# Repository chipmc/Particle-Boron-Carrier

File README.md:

# Particle-Boron-Carrier-v1.8
This is a carrier board for 3rd Generation Particle Devices (Boron and Argon).  It is intended to support use in outdoor environments and remote locations.  It includes the following capabilities:
* ESD and Short protection (Fuse, TVS and Varistors)
* Support for Solar charging (Large by-pass cap on DC-In and TMP-32 temp sensor to manage safe charging)
* Programmable Watchdog timer (AB1805)
* Real Time Clock with backup to the main LiPO battery (AB1805)
* On/Off switch using a high-side P-MOSFETS
* User Button for custom usage
* Connectors for IO including compatibility with Spankfun Qwiic and Adafruit Stemma (JST ST/SR)
* Footprint for a LoRA Radio module

Key Pin definitions for the FeatherWing Pins
 * Left Side (16 pins)
 Left Side (16 pins)
 * !RESET -
 * 3.3V -
 * !MODE -
 * GND -
 * D19 - A0 -               
 * D18 - A1 -               
 * D17 - A2 -               
 * D16 - A3 -
 * D15 - A4 -               Internal (TMP32) Temp Sensor
 * D14 - A5 / SPI SS -      RFM9x
 * D13 - SCK - SPI Clock -  
 * D12 - MO - SPI MOSI -    RFM9x
 * D11 - MI - SPI MISO -    RFM9x
 * D10 - UART RX -
 * D9 - UART TX -

 Right Size (12 pins)
 * Li+
 * ENABLE
 * VUSB -
 * D8 -                     Wake Connected to Watchdog Timer
 * D7 -                     Blue Led
 * D6 -                     
 * D5 -                     
 * D4 -                     User Switch
 * D3 -
 * D2 -                     RFM9x
 * D1 - SCL - I2C Clock -   FRAM / RTC and I2C Bus
 * D0 - SDA - I2C Data -    FRAM / RTX and I2C Bus

To see minimal code that will exercise the carrier board see this repository:
https://github.com/chipmc/CarrierTest3rdGen

 This board was developed in partnership with the Particle community See this thread for details on this board's development:
 https://community.particle.io/t/boron-xenon-argon-carrier-for-outdoor-applications/48750/213

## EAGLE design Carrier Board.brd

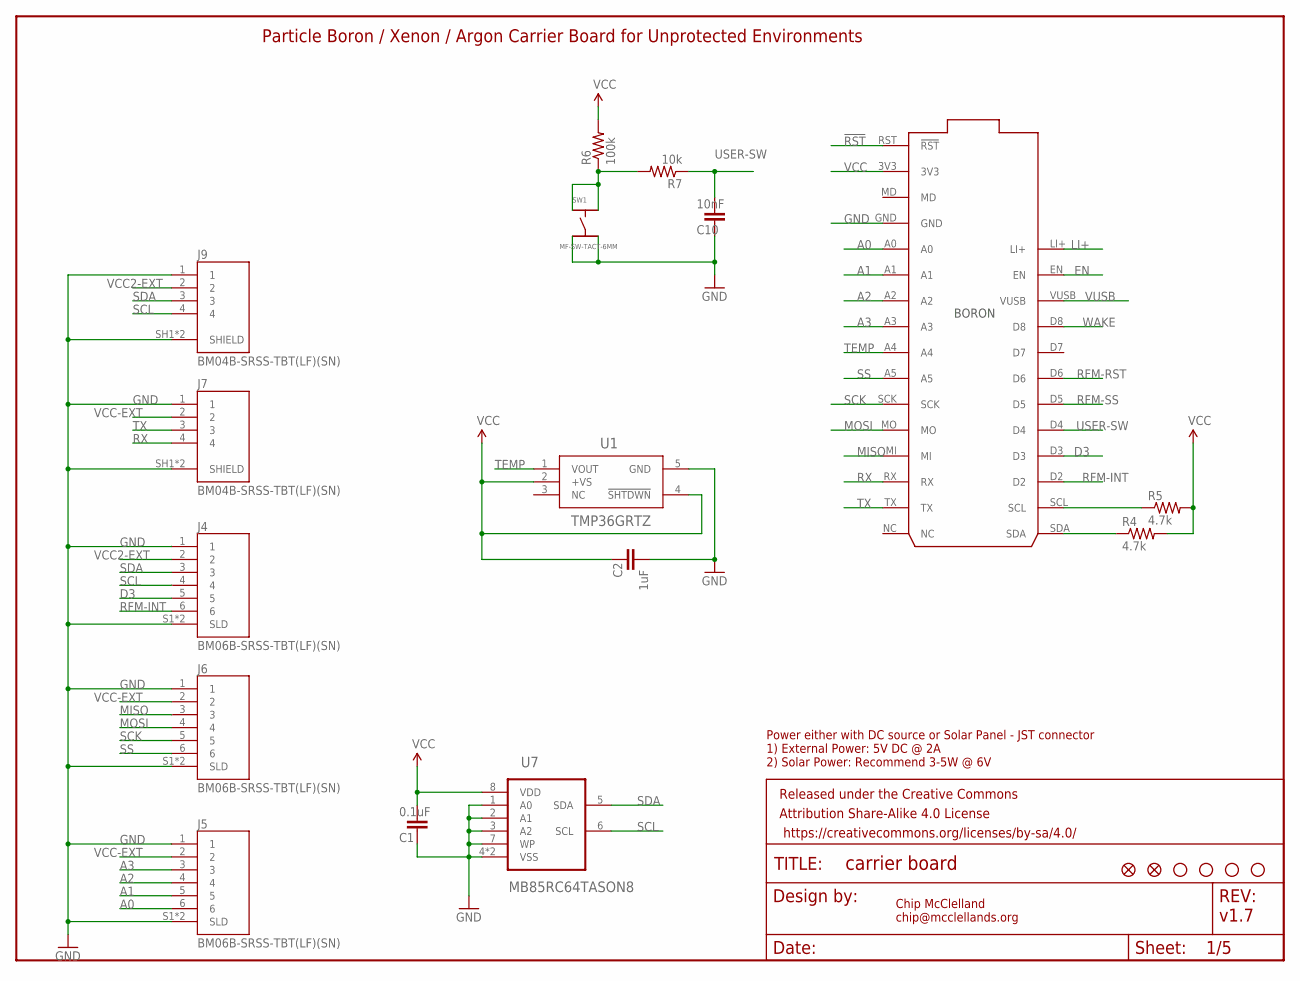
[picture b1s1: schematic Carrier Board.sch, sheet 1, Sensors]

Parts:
C1: 0.1uF; 0805@1; MPN MF-CAP-0805-0.1uF
C2: 1uF; 0805@1; MPN MF-CAP-0805-1uF
C10: 10nF; 0805@1; MPN 08051C103K4T2A
FD1, FD2: FIDUCIALUFIDUCIAL; FIDUCIAL-MICRO
FRAME1: FRAME-LETTER; CREATIVE_COMMONS
J4, J5, J6: BM06B-SRSS-TBT(LF)(SN); JST_BM06B-SRSS-TB(LF)(SN)
J7, J9: BM04B-SRSS-TBT(LF)(SN); CONN_BM04B-SRSS-TBT(LF)(SN)
JP3, JP4, JP5, JP6: STAND-OFF
P1: Particle Boron / Xenon / Argon; PARTICLE-DEVICES_BORON
R4, R5: 4.7k; 0805; MPN MF-RES-0805-4.7K
R6: 100k; 0805; MPN MF-RES-0805-100K
R7: 10k; 0805; MPN MF-RES-0805-10K
SW1: MF-SW-TACT-6MM; TACT6MM
U1: TMP36GRTZ; RJ_5_ADI; MANUFACTURER_PART_NUMBER TMP36GRTZ-REEL7
U7: MB85RC64TASON8; SON50P200X300X75-9N

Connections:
!RST: P1.RST (!RST); also elsewhere on the board
A0: J5.6, P1.A0
A1: J5.5, P1.A1
A2: J5.4, P1.A2
A3: J5.3, P1.A3
D3: J4.5, P1.D3; also elsewhere on the board
EN: P1.EN; also elsewhere on the board
GND: C1.2, C2.2, C10.2, J4.1, J4.S1 (SLD), J4.S2 (SLD), J5.1, J5.S1 (SLD), J5.S2 (SLD), J6.1, J6.S1 (SLD), J6.S2 (SLD), J7.1, J7.SH1 (SHIELD), J7.SH2 (SHIELD), J9.1, J9.SH1 (SHIELD), J9.SH2 (SHIELD), P1.GND, SW1.P$3, SW1.P$4, U1.5 (GND), U7.1 (A0), U7.2 (A1), U7.3 (A2), U7.4 (VSS), U7.7 (WP), U7.9 (VSS); also elsewhere on the board
LI+: P1.LI+; also elsewhere on the board
MISO: J6.3, P1.MI; also elsewhere on the board
MOSI: J6.4, P1.MO; also elsewhere on the board
unnamed: R6.1, R7.2, SW1.P$1, SW1.P$2
RFM-INT: J4.6, P1.D2; also elsewhere on the board
RFM-RST: P1.D6; also elsewhere on the board
RFM-SS: P1.D5; also elsewhere on the board
RX: J7.4, P1.RX
SCK: J6.5, P1.SCK; also elsewhere on the board
SCL: J4.4, J9.4, P1.SCL, R5.1, U7.6 (SCL); also elsewhere on the board
SDA: J4.3, J9.3, P1.SDA, R4.1, U7.5 (SDA); also elsewhere on the board
SS: J6.6, P1.A5
TEMP: P1.A4, U1.1 (VOUT)
TX: J7.3, P1.TX
USER-SW: C10.1, P1.D4, R7.1
VCC: C1.1, C2.1, P1.3V3, R4.2, R5.2, R6.2, U1.2 (+VS), U1.4 (!SHTDWN), U7.8 (VDD); also elsewhere on the board
VCC2-EXT: J4.2, J9.2; also elsewhere on the board
VCC-EXT: J5.2, J6.2, J7.2; also elsewhere on the board
VUSB: P1.VUSB; also elsewhere on the board
WAKE: P1.D8; also elsewhere on the board

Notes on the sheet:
Chip McClelland chip@mcclellands.org
v1.7
Power either with DC source or Solar Panel - JST connector 1) External Power: 5V DC @ 2A 2) Solar Power: Recommend 3-5W @ 6V
Particle Boron / Xenon / Argon Carrier Board for Unprotected Environments

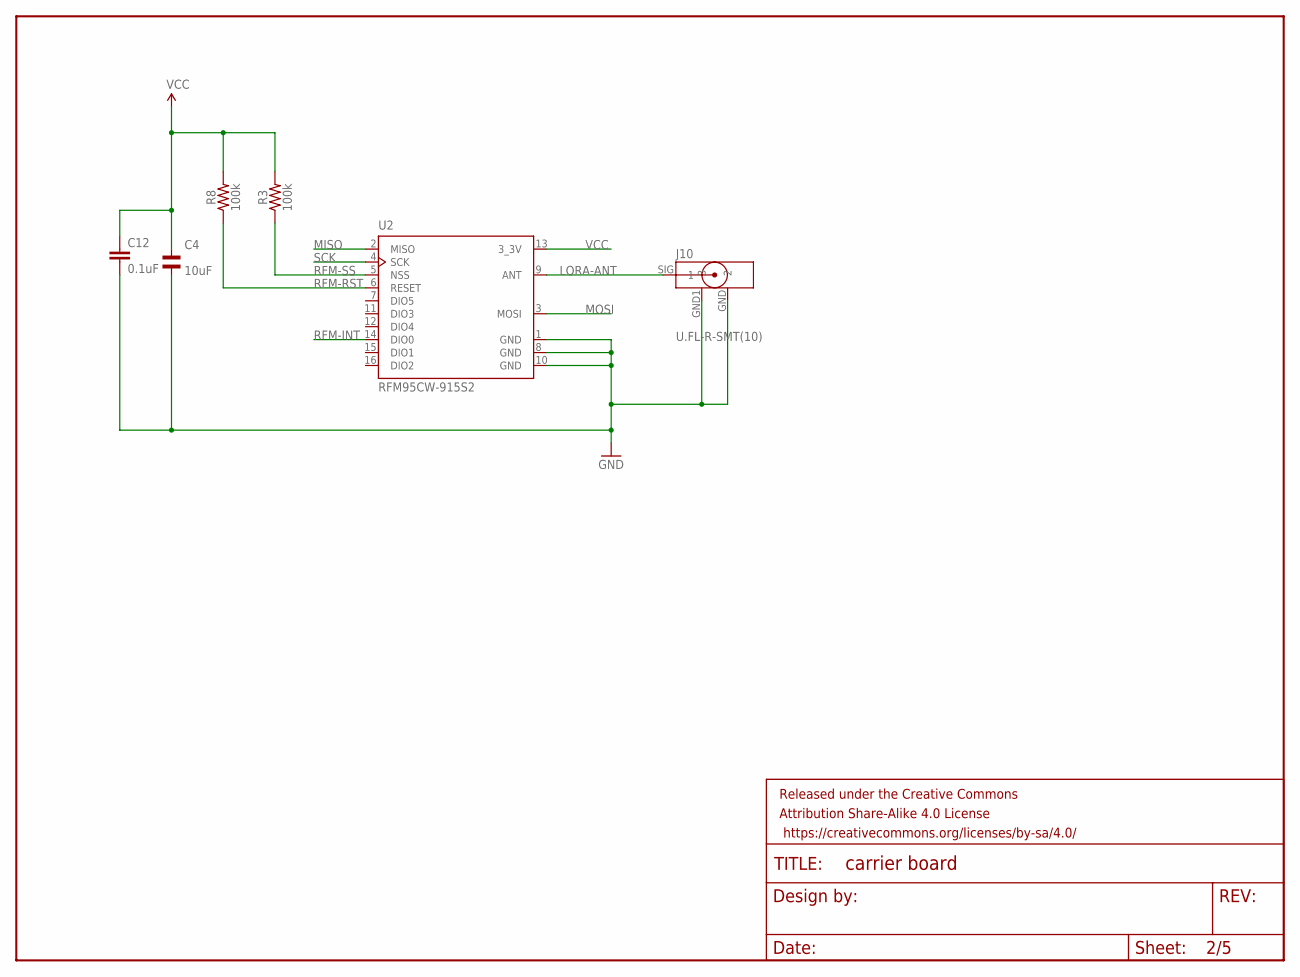
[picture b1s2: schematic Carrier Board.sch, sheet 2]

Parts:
C4: 10uF; C1206
C12: 0.1uF; 0805@1
FRAME4: FRAME-LETTERNO_PACKAGE; DUMMY
J10: U.FL-R-SMT(10)
R3, R8: 100k; 0805
U2: RFM95CW-915S2; XCVR_RFM95W-868S2

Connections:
GND: C4.P$2, C12.2, J10.GND (2), J10.GND1 (3), U2.1 (GND), U2.8 (GND), U2.10 (GND); also elsewhere on the board
LORA-ANT: J10.SIG (1), U2.9 (ANT)
MISO: U2.2 (MISO); also elsewhere on the board
MOSI: U2.3 (MOSI); also elsewhere on the board
RFM-INT: U2.14 (DIO0); also elsewhere on the board
RFM-RST: R8.1, U2.6 (RESET); also elsewhere on the board
RFM-SS: R3.1, U2.5 (NSS); also elsewhere on the board
SCK: U2.4 (SCK); also elsewhere on the board
VCC: C4.P$1, C12.1, R3.2, R8.2, U2.13 (3_3V); also elsewhere on the board

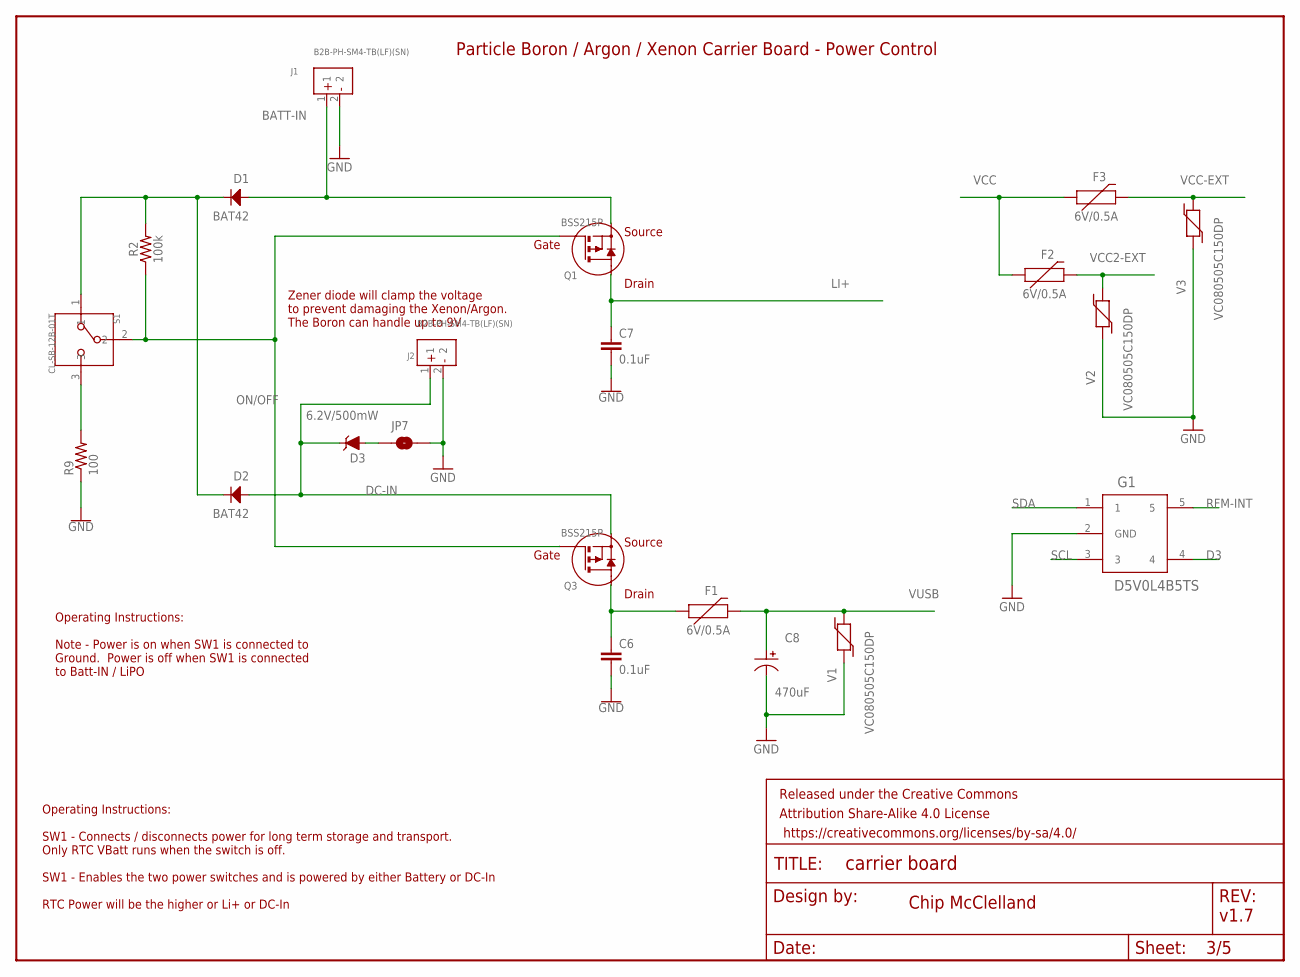
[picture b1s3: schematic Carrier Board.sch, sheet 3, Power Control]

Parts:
C6, C7: 0.1uF; 0805@1; MPN MF-CAP-0805-0.1uF
C8: 470uF; CP10MM; MPN MF-CAP-10MM-470uF
D1, D2: BAT42; SOD-123
D3: 6.2V/500mW; PANASONIC_SMINI2-F5-B; MPN TDZ6V2J,115
F1: 6V/0.5A; 1206; MPN 046801.5NR
F2, F3: 6V/0.5A; 1206; MPN 0466.500NR
FRAME2: FRAME-LETTER; CREATIVE_COMMONS
G1: D5V0L4B5TS; SOT-23-5; MPN D5V0L4B5TS-7
J1, J2: B2B-PH-SM4-TB(LF)(SN); JST_B2B-PH-SM4-TB(LF)(SN)
JP7: JUMPER-SMT_2_NO_SILK; SMT-JUMPER_2_NO_SILK
Q1, Q3: BSS215P; SOT-23_3L_ONS-M
R2: 100k; 0805
R9: 100; 0805; MPN MF-RES-0805-100
S1: CL-SB-12B-01T; CL-SB-12B
V1, V2, V3: VC080505C150DP; 0805; MPN VC080505C150DP

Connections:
BATT-IN: D1.ANODE, J1.1, Q1.2 (SOURCE); also elsewhere on the board
D3: G1.4; also elsewhere on the board
DC-IN: D2.ANODE, D3.C, J2.1, Q3.2 (SOURCE)
GND: C6.2, C7.2, C8.P$2, G1.2 (GND), J1.2, J2.2, JP7.1, R9.1, V1.1, V2.1, V3.1; also elsewhere on the board
LI+: C7.1, Q1.3 (DRAIN); also elsewhere on the board
unnamed: D3.A, JP7.2
unnamed: C6.1, F1.1, Q3.3 (DRAIN)
unnamed: D1.CATHODE, D2.CATHODE, R2.2, S1.1
unnamed: R9.2, S1.3
ON/OFF: Q1.1 (GATE), Q3.1 (GATE), R2.1, S1.2
RFM-INT: G1.5; also elsewhere on the board
SCL: G1.3; also elsewhere on the board
SDA: G1.1; also elsewhere on the board
VCC: F2.1, F3.1; also elsewhere on the board
VCC2-EXT: F2.2, V2.2; also elsewhere on the board
VCC-EXT: F3.2, V3.2; also elsewhere on the board
VUSB: C8.P$1, F1.2, V1.2; also elsewhere on the board

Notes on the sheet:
Particle Boron / Argon / Xenon Carrier Board - Power Control
Chip McClelland
v1.7
Operating Instructions: SW1 - Connects / disconnects power for long term storage and transport. Only RTC VBatt runs when the switch is off. SW1 - Enables the two power switches and is powered by either Battery or DC-In RTC Power will be the higher or Li+ or DC-In
Zener diode will clamp the voltage to prevent damaging the Xenon/Argon. The Boron can handle up to 9V
Operating Instructions: Note - Power is on when SW1 is connected to Ground. Power is off when SW1 is connected to Batt-IN / LiPO

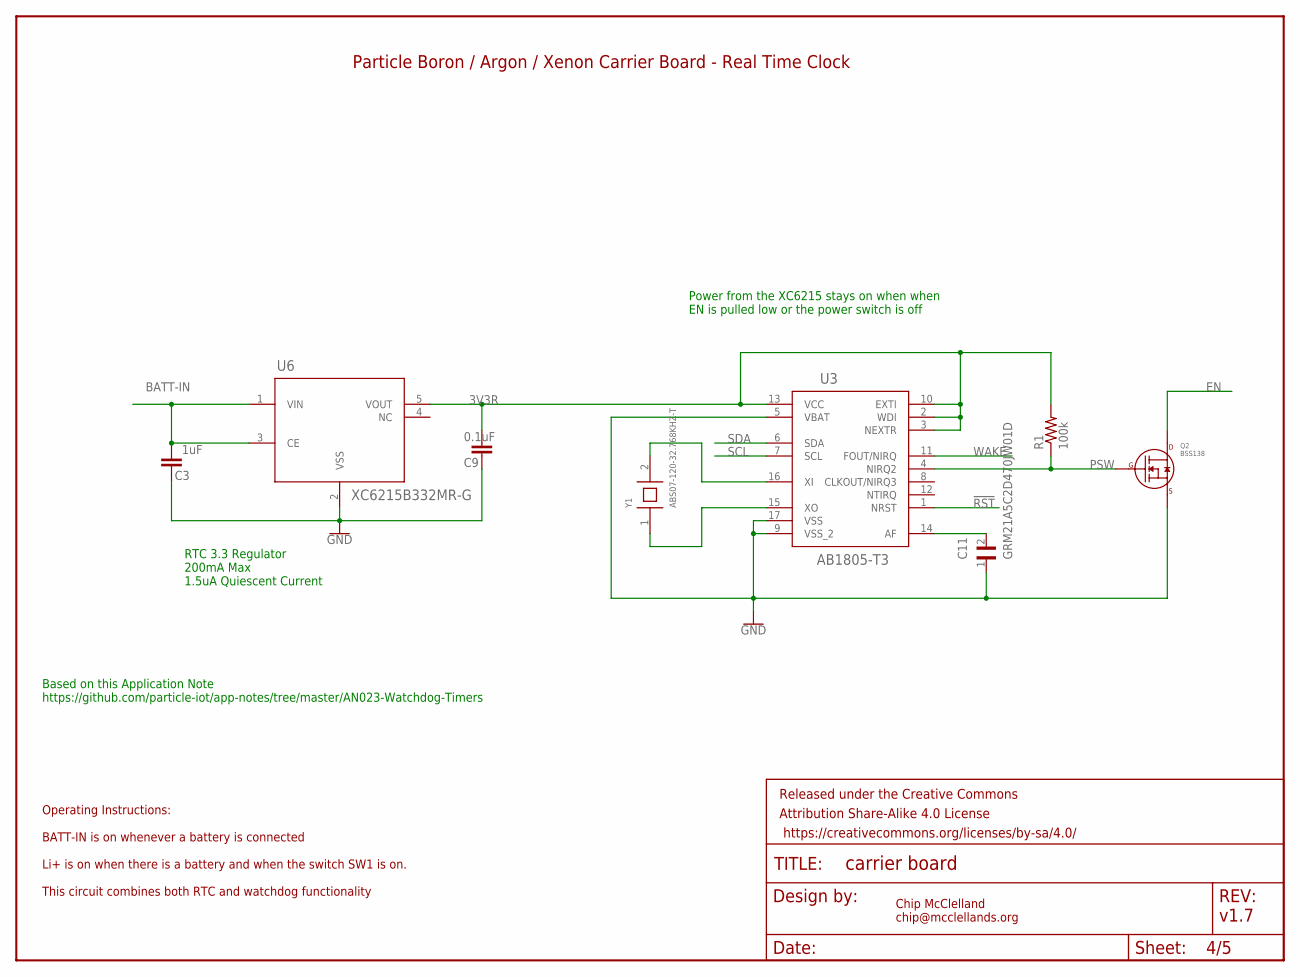
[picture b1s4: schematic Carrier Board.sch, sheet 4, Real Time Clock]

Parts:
C3: 1uF; 0805@1; MPN MF-CAP-0805-1uF
C9: 0.1uF; 0805@1; MPN MF-CAP-0805-0.1uF
C11: GRM21A5C2D470JW01D; CAPC2012X100N
FRAME3: FRAME-LETTER; CREATIVE_COMMONS
Q2: BSS138; SOT-23_3L_ONS
R1: 100k; 0805; MPN MF-RES-0805-100K
U3: AB1805-T3; QFN_16_ABR
U6: XC6215B332MR-G; SOT-25_TOR
Y1: ABS07-120-32.768KHZ-T; XTAL_ABS07-120-32.768KHZ-T

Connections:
3V3R: C9.1, R1.2, U3.2 (WDI), U3.3 (NEXTR), U3.10 (EXTI), U3.13 (VCC), U6.5 (VOUT)
!RST: U3.1 (NRST); also elsewhere on the board
BATT-IN: C3.2, U6.1 (VIN), U6.3 (CE); also elsewhere on the board
EN: Q2.3 (DRAIN); also elsewhere on the board
GND: C3.1, C9.2, C11.1, Q2.2 (SOURCE), U3.5 (VBAT), U3.9 (VSS_2), U3.17 (VSS), U6.2 (VSS); also elsewhere on the board
unnamed: U3.15 (XO), Y1.1
unnamed: U3.16 (XI), Y1.2
unnamed: C11.2, U3.14 (AF)
PSW: Q2.1 (GATE), R1.1, U3.4 (NIRQ2)
SCL: U3.7 (SCL); also elsewhere on the board
SDA: U3.6 (SDA); also elsewhere on the board
WAKE: U3.11 (FOUT/NIRQ); also elsewhere on the board

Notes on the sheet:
Operating Instructions: BATT-IN is on whenever a battery is connected Li+ is on when there is a battery and when the switch SW1 is on. This circuit combines both RTC and watchdog functionality
Particle Boron / Argon / Xenon Carrier Board - Real Time Clock
Chip McClelland chip@mcclellands.org
v1.7
RTC 3.3 Regulator 200mA Max 1.5uA Quiescent Current
Power from the XC6215 stays on when when EN is pulled low or the power switch is off
Based on this Application Note https://github.com/particle-iot/app-notes/tree/master/AN023-Watchdog-Timers

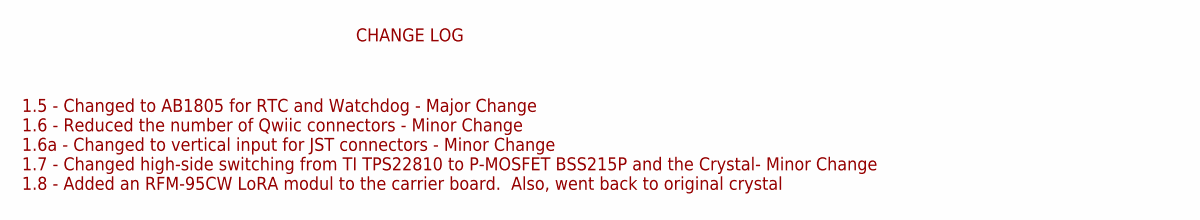
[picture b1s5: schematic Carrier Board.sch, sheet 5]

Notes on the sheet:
CHANGE LOG
1.5 - Changed to AB1805 for RTC and Watchdog - Major Change 1.6 - Reduced the number of Qwiic connectors - Minor Change 1.6a - Changed to vertical input for JST connectors - Minor Change 1.7 - Changed high-side switching from TI TPS22810 to P-MOSFET BSS215P and the Crystal- Minor Change 1.8 - Added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

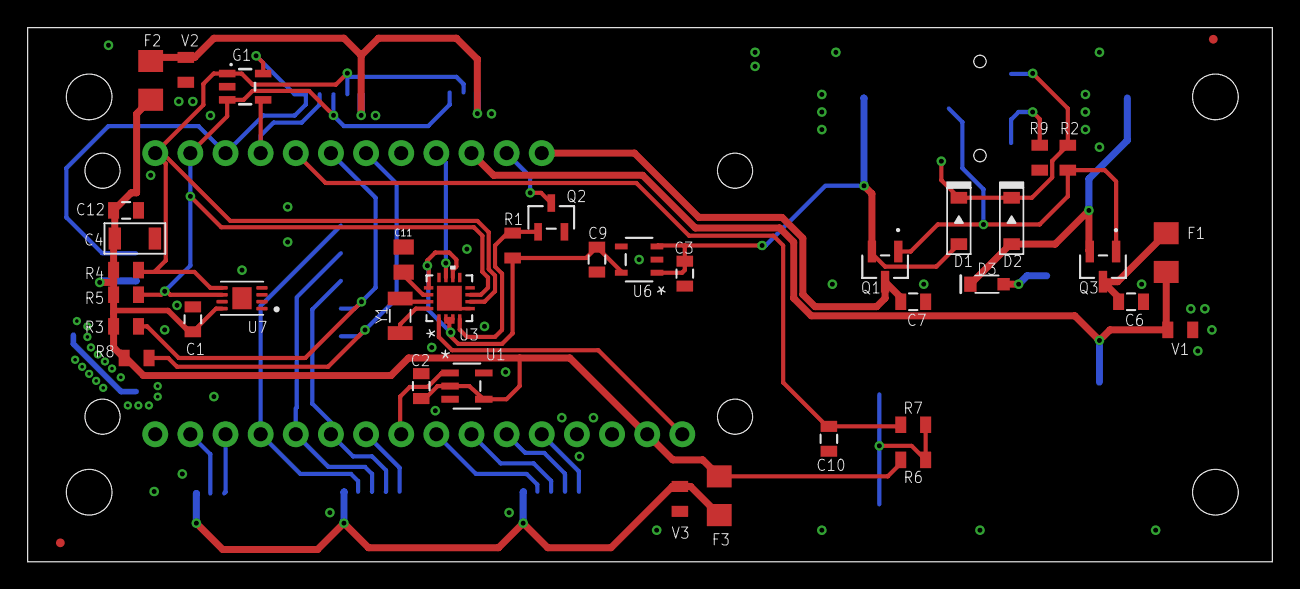
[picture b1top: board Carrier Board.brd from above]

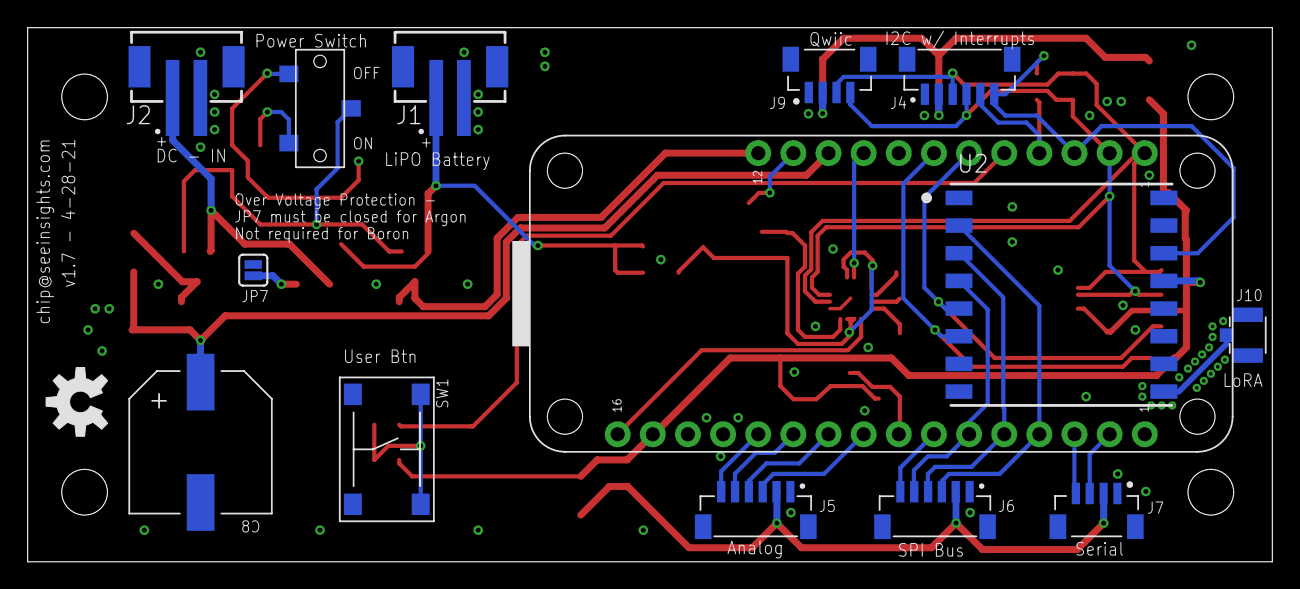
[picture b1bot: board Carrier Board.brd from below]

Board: 2 copper layers, 90.0 x 38.6 mm, 62 parts (15 on the bottom side), 41 nets.

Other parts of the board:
U$2: OSHW-LOGO-M

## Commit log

2020-11-20 Updated for Macrofab
2021-02-15 Updated read me
2021-02-15 Latest Version
2021-04-07 Updated FRAM footprint to address stock issue
2021-04-07 New Readme
2022-12-29 Fully functional
2022-12-29 Added Images
2022-12-29 Updated imagery
2023-08-01 Added LoRA

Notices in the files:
parts and their libraries:
SparkFun-Aesthetics: Licensing: Creative Commons ShareAlike 4.0 International - https://creativecommons.org/licenses/by-sa/4.0
SparkFun-Aesthetics: Released under the Creative Commons Attribution Share-Alike 4.0 License
SparkFun-Aesthetics: https://creativecommons.org/licenses/by-sa/4.0
